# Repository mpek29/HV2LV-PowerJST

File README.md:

# HV2LV-PowerJST

## 🚀 Overview

**HV2LV-PowerJST** is an open-source PCB designed to step down **4.8V - 15V** to a stable **3.3V** output using an **AMS1117 voltage regulator**. The board features **JST-PH connectors** for easy integration into embedded projects, IoT devices, and prototyping setups.  

## 🎯 Purpose
- 🔌 **Efficient power conversion**: Converts input voltages from **4.8V to 15V** down to a fixed **3.3V**. 
- 📏 **Compact and Adafruit-compatible**: Designed to fit within Adafruit's standard PCB footprint.
- 🛠️ **Open-source and customizable**: Modify and adapt the design to suit your specific needs.

## 📝 Features
| 🏷️ Feature        | 🔍 Description |
|----------------|-------------|
| ⚡ **Input Voltage** | 4.8V - 15V |
| 🔋 **Output Voltage** | 3.3V (fixed) |
| 🛠️ **Regulator** | AMS1117-3.3 |
| 🔌 **Connector 1** | JST-PH (Input Voltage) |
| 🔌 **Connector 2** | JST-PH (3.3V Output) |
| 🔧 **Capacitors** | 4 decoupling capacitors for stability |
| 🖥️ **PCB Design** | Open-source & customizable |
| 🌍 **Use Cases** | Powering 3.3V embedded systems, IoT devices, and sensors |

## 📐 PCB Design Preview
| 📜 Schematic | 🖥️ PCB Layout | 🏗️ 3D |
|-----------|-----------|-----------|
|  |  |  |

## 🌟 License
This project is open-source. Feel free to use, modify, and contribute! 🚀

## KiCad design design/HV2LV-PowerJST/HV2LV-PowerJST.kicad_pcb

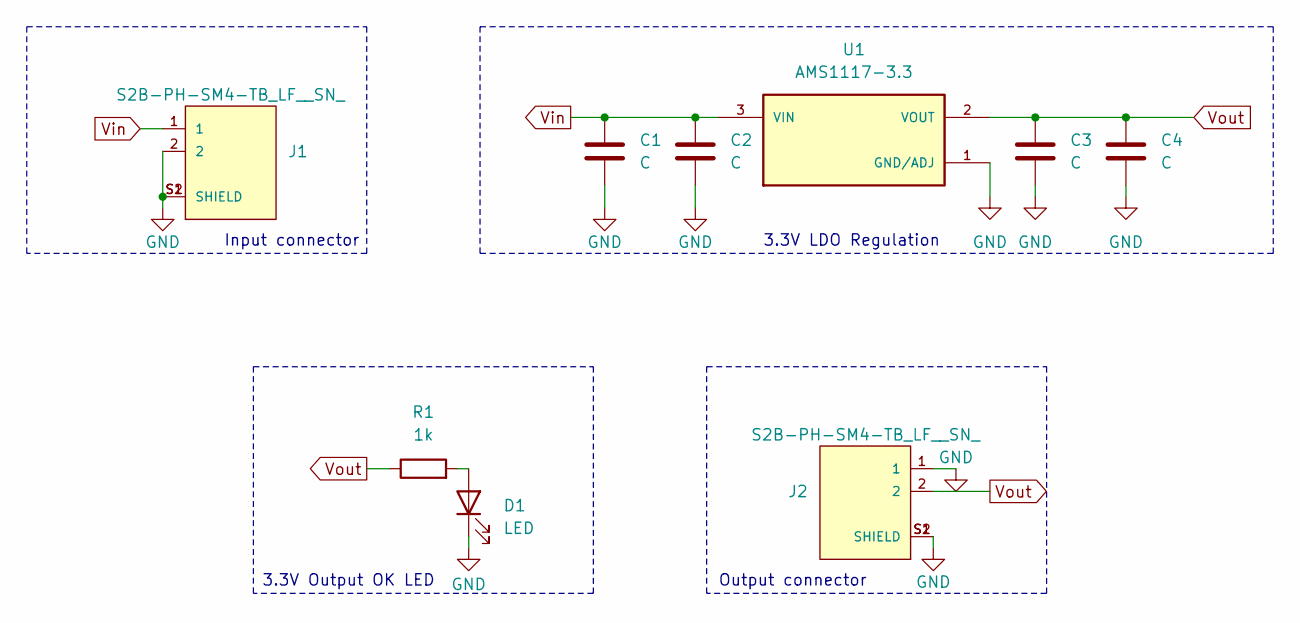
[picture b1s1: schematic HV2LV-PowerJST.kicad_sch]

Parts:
C1, C2, C3, C4: C; C_0603_1608Metric
D1: LED; LED_1206_3216Metric
J1, J2: S2B-PH-SM4-TB_LF__SN_; JST_S2B-PH-SM4-TB_LF__SN_
R1: 1k; R_1206_3216Metric
U1: AMS1117-3.3; SOT229P700X180-4N; PARTREV N/A

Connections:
GND: C1.2, C2.2, C3.2, C4.2, D1.1 (K), J1.2, J1.S1 (SHIELD), J1.S2 (SHIELD), J2.1, J2.S1 (SHIELD), J2.S2 (SHIELD), U1.1 (GND/ADJ)
unnamed: D1.2 (A), R1.2
Vin: C1.1, C2.1, J1.1, U1.3 (VIN)
Vout: C3.1, C4.1, J2.2, R1.1, U1.2 (VOUT)

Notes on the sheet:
Input connector
Output connector
3.3V Output OK LED
3.3V LDO Regulation

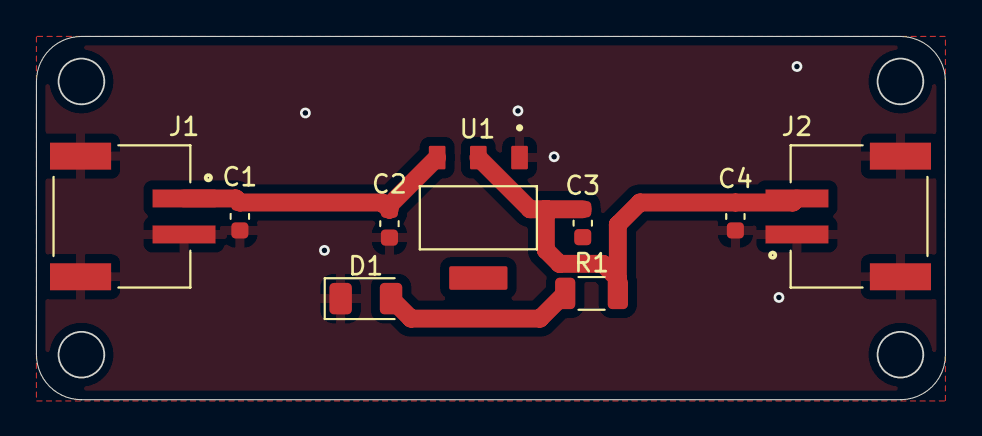
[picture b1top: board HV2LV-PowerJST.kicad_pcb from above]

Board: 2 copper layers, 50.5 x 20.1 mm, 9 parts (0 on the bottom side), 4 nets.

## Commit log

2025-02-19 Addition of some images to better describe the project
2025-03-03 best adaptation to adafruit swirly grill
